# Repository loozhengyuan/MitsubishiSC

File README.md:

# MitsubishiSC

Smart controller for Mitsubishi Electric HVAC systems.

## Usage

### Upgrade

Download the app image from the [latest release](https://github.com/loozhengyuan/MitsubishiSC/releases/latest) and flash it with [`esptool`](https://docs.espressif.com/projects/esptool/), which keeps the Matter commissioning data:

```shell
esptool --chip esp32c6 write-flash 0x20000 MitsubishiSC-vX.Y.Z-fw-esp32c6-thread-app.bin
```

_NOTE: If the device does not boot after upgrading, flash the full image at `0x0` instead, which erases the Matter commissioning data. Neither image contains the per-device [factory data partition](#factory-data-partition)._

## Development

The firmware is built with [Espressif ESP-IDF](https://github.com/espressif/esp-idf) and [Espressif Matter SDK](https://github.com/espressif/esp-matter), and requires **ESP-IDF v5.5.5** to build and flash.

### Configuration

- `sdkconfig.defaults`: Baseline configuration for Matter
- `sdkconfig.debug`: Enables debug logging
- `sdkconfig.mfgpart`: Enables [Factory Data Providers](https://docs.espressif.com/projects/esp-matter/en/latest/esp32/developing.html#factory-data-providers)
- `sdkconfig.lowpower`: Enables power-saving configurations
- `sdkconfig.thread`: Enables Thread mode

```shell
idf.py -D SDKCONFIG_DEFAULTS='sdkconfig.defaults;sdkconfig.mfgpart;sdkconfig.thread' set-target 'esp32c6'
```

### Factory Data Partition

For the initial flashing, we need to generate the factory data partition using the [`esp-matter-mfg-tool`](https://github.com/espressif/esp-matter-tools/tree/main/mfg_tool). For convenience, we can use the [`./scripts/generate.sh`](./scripts/generate.sh) script:

```shell
./scripts/generate.sh
```

Thereafter, we can flash the initial factory partition (substitute `ID` based on the generated files):

```shell
idf.py flash --extra-args="0x3E0000 $(pwd)/out/fff2_8001/${ID}/${ID}-partition.bin"
```

### Build

```shell
idf.py build
```

### Flash

```shell
idf.py flash
```

### Release

The firmware and hardware share a single [semantic version](https://semver.org) in [`VERSION`](./VERSION), where `MAJOR.MINOR` is the board version. To release, bump `VERSION` in a pull request, then run the [`ci`](https://github.com/loozhengyuan/MitsubishiSC/actions/workflows/ci.yml) workflow on `main` with `release` checked.

## Concepts

### Protocol

The CN105 connector exposes the UART interface via the RX and TX pins. As [discovered by Hadley Rich](https://nicegear.nz/blog/hacking-a-mitsubishi-heat-pump-air-conditioner/), this uses 5V TTL 2400 8-E-1.

Since the ESP32/STM32 runs on 3.3V while the UART runs on 5V, there is a need to use a logic level shifter. [BSS138](https://www.onsemi.com/pdf/datasheet/bss138-d.pdf) is a N-channel MOSFET with a low $V_{GS(th)}$, which makes it [more ideal than other NMOS components](https://electronics.stackexchange.com/questions/242424/what-can-i-replace-a-bss138-n-channel-mosfet-with).

For more information about the packets, refer to [mUART Protocol Reference](https://muart-group.github.io/developer/packet-reference).

## Hardware

### MCU

As part of the project goals, we want to build a device that leverages on the [Matter](https://csa-iot.org/all-solutions/matter/) standard for maximum compatibility and [Thread](https://www.threadgroup.org) for low-power, low-latency performance. The selected microcontroller should have the following features:

- Support for WiFi and Thread
- Support for Matter over WiFi/Thread

| Manufacturer         | MPN                                                                                                                       | Type | Price                                                                                                                             |
| -------------------- | ------------------------------------------------------------------------------------------------------------------------- | ---- | --------------------------------------------------------------------------------------------------------------------------------- |
| Espressif Systems    | [`ESP32-C6FH4`](https://www.espressif.com/sites/default/files/documentation/esp32-c6_datasheet_en.pdf)                    | SoC  |                                                                                                                                   |
| Espressif Systems    | [`ESP32-C6-MINI-1`](https://www.espressif.com/sites/default/files/documentation/esp32-c6-mini-1_mini-1u_datasheet_en.pdf) | SoC  |                                                                                                                                   |
| STMicroelectronics   | [`STM32WB55CGU6`](https://www.st.com/resource/en/datasheet/stm32wb55cg.pdf)                                               | SoC  | [US$3.48](https://www.lcsc.com/product-detail/Microcontroller-Units-MCUs-MPUs-SOCs_STMicroelectronics-STM32WB55CGU6_C404023.html) |
| STMicroelectronics   | [`STM32WB5MMG`](https://www.st.com/resource/en/datasheet/stm32wb5mmg.pdf)                                                 | SoC  |                                                                                                                                   |
| Nordic Semiconductor | [`NRF52840-QIAA-R`](https://docs-be.nordicsemi.com/bundle/ps_nrf52840/attach/nRF52840_PS_v1.9.pdf)                        | SoC  | [US$3.41](https://www.lcsc.com/product-detail/RF-Transceiver-ICs_Nordic-Semicon-NRF52840-QIAA-R_C190794.html)                     |

_NOTE: The SKUs from [LCSC](https://www.lcsc.com) Popular Products are preferred to ensure good price and supply._

### Connector

The Mitsubishi Electric air conditioner has a `CN105` port that appears to be a [JST PA](https://www.jst.com/products/appliance-connectors/pa-family/) connector. To fit this, we should use `PAP-05V-S` housing with `SPHD-001T-P0.5`/`SPHD-002T-P0.5` contacts.

DigiKey stocks the `APALPA22K305`/`APAPA22K305` pre-crimped cables in 22 AWG, 12" cables.

According to the [LCSC](https://www.lcsc.com) team, the HCTL [`HC-PA-5Y`](https://www.lcsc.com/product-detail/Rectangular-Connectors-Housings_HCTL_C2962360.html) and [`HC-PA-T`](https://www.lcsc.com/product-detail/Line-Pressing-Terminals_HCTL-HC-PA-T_C2962368.html) are equivalent replacements for this part.

### Power Supply

The STM32/ESP32 runs on 3.3V but the `CN105` connector only exposes 12V and 5V power rails.

To power the MCU, we use a low-dropout linear regulator to regulate 5V to 3.3V. `MCP1700` is chosen for its low quiescent current ($I_Q$) but any modern LDO should work.

## License

[MIT](https://choosealicense.com/licenses/mit/)

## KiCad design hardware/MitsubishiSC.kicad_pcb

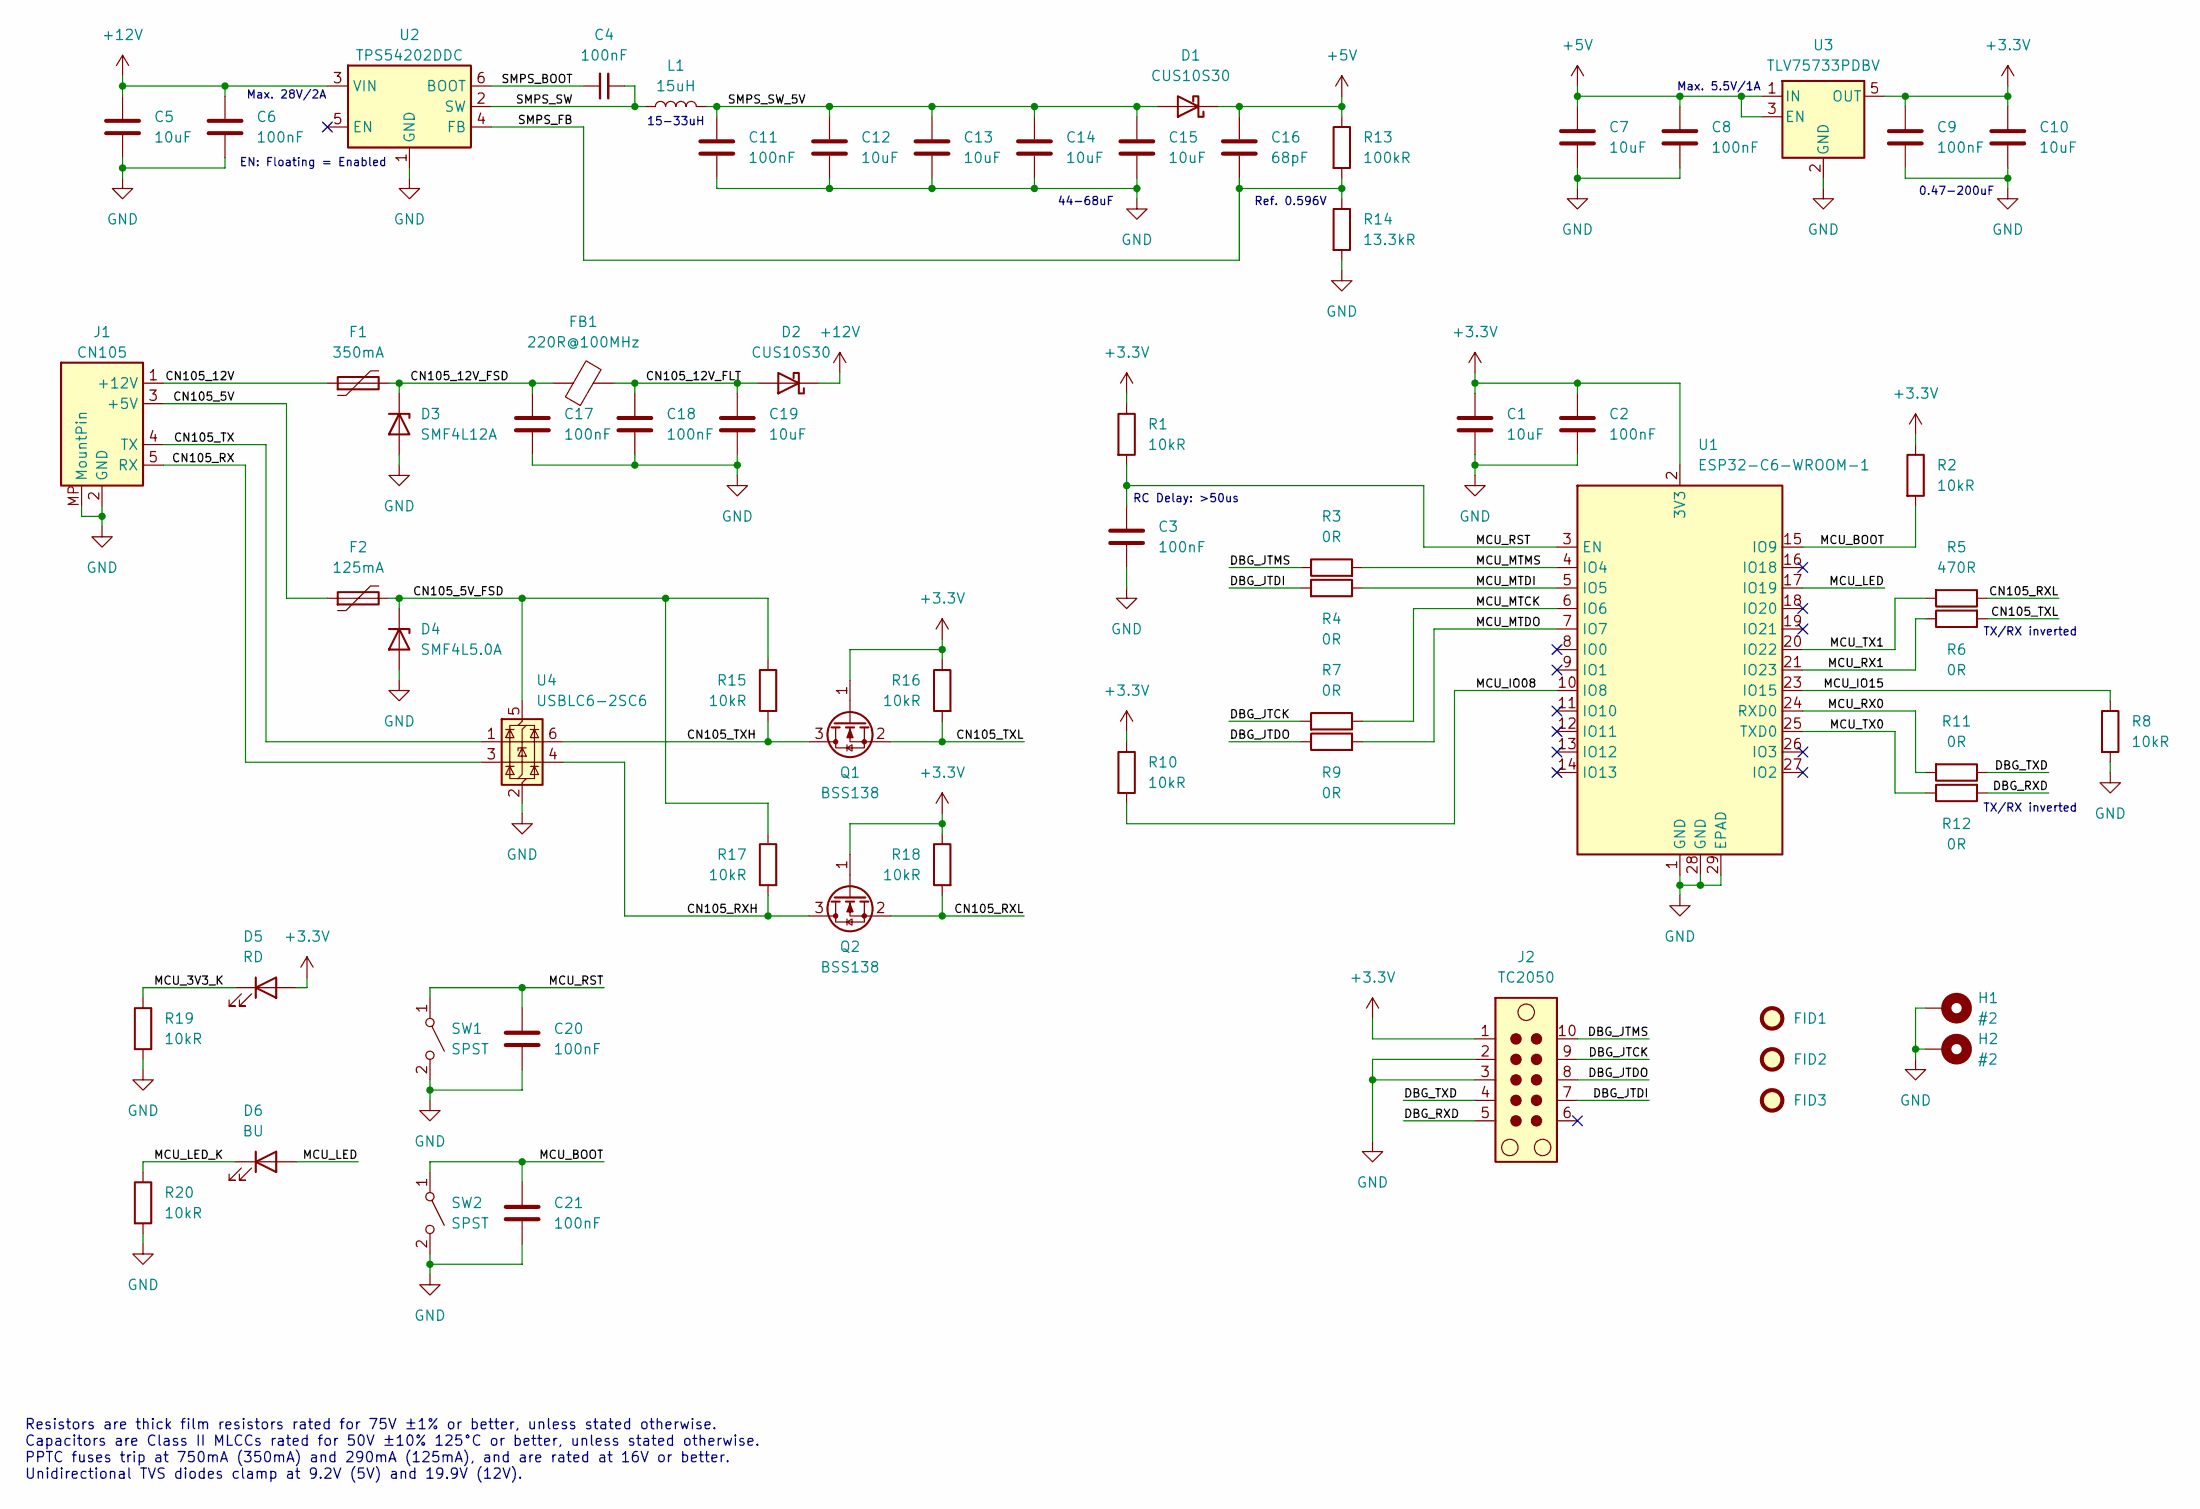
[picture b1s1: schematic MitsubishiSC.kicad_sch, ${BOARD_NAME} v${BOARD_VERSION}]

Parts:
C1, C5, C7, C10, C12, C13, C14, C15, C19: 10uF; C_1206_3216Metric; Manufacturer Part Number CL31B106KBHNNNE
C2, C3, C4, C6, C8, C9, C11, C17, C18, C20, C21: 100nF; C_0603_1608Metric; Manufacturer Part Number CL10B104KC8NNNC
C16: 68pF; C_0603_1608Metric; Manufacturer Part Number CL10C680JB8NNNC
D1, D2: CUS10S30; D_SOD-323; Manufacturer Part Number CUS10S30,H3F
D3: SMF4L12A; D_SOD-123F; Manufacturer Part Number SMF4L12A
D4: SMF4L5.0A; D_SOD-123F; Manufacturer Part Number SMF4L5.0A
D5: RD; LED_0805_2012Metric; Manufacturer Part Number XL-2012SURC
D6: BU; LED_0805_2012Metric; Manufacturer Part Number XL-2012UBC
F1: 350mA; Fuse_1206_3216Metric; Manufacturer Part Number 1206L035/16YR
F2: 125mA; Fuse_1206_3216Metric; Manufacturer Part Number 1206L012WR
FB1: 220R@100MHz; L_0805_2012Metric; Manufacturer Part Number BLM21PG221SN1D
FID1, FID2, FID3: Fiducial; Fiducial_1mm_Mask2mm
H1, H2: #2; MountingHole_2.5mm_Pad_Via; Manufacturer Part Number 1553WTS100
J1: CN105; JST_PA_SM05B-PASS_1x05-1MP_P2.00mm_Horizontal; Manufacturer Part Number SM05B-PASS-TBT(LF)(SN)
J2: TC2050; Tag-Connect_TC2050-IDC-NL_2x05_P1.27mm_Vertical
L1: 15uH; L_TDK_VLS6045EX_VLS6045AF; Manufacturer Part Number VLS6045EX-150M
Q1, Q2: BSS138; SOT-23; Manufacturer Part Number BSS138
R1, R2, R8, R10, R15, R16, R17, R18, R19, R20: 10kR; R_0603_1608Metric; Manufacturer Part Number RC0603FR-0710KL
R3, R4, R6, R7, R9, R11, R12: 0R; R_0603_1608Metric; Manufacturer Part Number RC0603FR-070RL
R5: 470R; R_0603_1608Metric; Manufacturer Part Number RC0603FR-07470RL
R13: 100kR; R_0603_1608Metric; Manufacturer Part Number RC0603FR-07100KL
R14: 13.3kR; R_0603_1608Metric; Manufacturer Part Number RC0603FR-0713K3L
SW1, SW2: SPST; SW_SPST_PTS810; Manufacturer Part Number GT-TC048D-H025-L1
U1: ESP32-C6-WROOM-1; Manufacturer Part Number ESP32-C6-WROOM-1-N8
U2: TPS54202DDC; SOT-23-6; Manufacturer Part Number TPS54202DDCR
U3: TLV75733PDBV; SOT-23-5; Manufacturer Part Number TLV75733PDBVR
U4: USBLC6-2SC6; SOT-23-6; Manufacturer Part Number USBLC6-2SC6

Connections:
+3.3V: C1.1, C2.1, C9.1, C10.1, D5.2 (A), J2.1, Q1.1 (G), Q2.1 (G), R1.1, R2.1, R10.1, R16.1, R18.1, U1.2 (3V3), U3.5 (OUT)
+5V: C7.1, C8.1, C16.1, D1.1 (K), R13.1, U3.1 (IN), U3.3 (EN)
+12V: C5.1, C6.1, D2.1 (K), U2.3 (VIN)
/CN105_5V: F2.1, J1.3 (+5V)
/CN105_5V_FSD: D4.1 (K), F2.2, R15.1, R17.1, U4.5 (VBUS)
/CN105_12V: F1.1, J1.1 (+12V)
/CN105_12V_FLT: C18.1, C19.1, D2.2 (A), FB1.2
/CN105_12V_FSD: C17.1, D3.1 (K), F1.2, FB1.1
/CN105_RX: J1.5 (RX), U4.3 (I/O2)
/CN105_RXH: Q2.3 (D), R17.2, U4.4 (I/O2)
/CN105_RXL: Q2.2 (S), R5.1, R18.2
/CN105_TX: J1.4 (TX), U4.1 (I/O1)
/CN105_TXH: Q1.3 (D), R15.2, U4.6 (I/O1)
/CN105_TXL: Q1.2 (S), R6.2, R16.2
/DBG_JTCK: J2.9, R7.2
/DBG_JTDI: J2.7, R4.2
/DBG_JTDO: J2.8, R9.1
/DBG_JTMS: J2.10, R3.1
/DBG_RXD: J2.5, R12.2
/DBG_TXD: J2.4, R11.1
/MCU_3V3_K: D5.1 (K), R19.1
/MCU_BOOT: C21.1, R2.2, SW2.1 (A), U1.15 (IO9)
/MCU_IO08: R10.2, U1.10 (IO8)
/MCU_IO15: R8.1, U1.23 (IO15)
/MCU_LED: D6.2 (A), U1.17 (IO19)
/MCU_LED_K: D6.1 (K), R20.1
/MCU_MTCK: R7.1, U1.6 (IO6)
/MCU_MTDI: R4.1, U1.5 (IO5)
/MCU_MTDO: R9.2, U1.7 (IO7)
/MCU_MTMS: R3.2, U1.4 (IO4)
/MCU_RST: C3.1, C20.1, R1.2, SW1.1 (A), U1.3 (EN)
/MCU_RX0: R11.2, U1.24 (RXD0)
/MCU_RX1: R6.1, U1.21 (IO23)
/MCU_TX0: R12.1, U1.25 (TXD0)
/MCU_TX1: R5.2, U1.20 (IO22)
/SMPS_BOOT: C4.1, U2.6 (BOOT)
/SMPS_FB: C16.2, R13.2, R14.1, U2.4 (FB)
/SMPS_SW: C4.2, L1.1, U2.2 (SW)
/SMPS_SW_5V: C11.1, C12.1, C13.1, C14.1, C15.1, D1.2 (A), L1.2
GND: C1.2, C2.2, C3.2, C5.2, C6.2, C7.2, C8.2, C9.2, C10.2, C11.2, C12.2, C13.2, C14.2, C15.2, C17.2, C18.2, C19.2, C20.2, C21.2, D3.2 (A), D4.2 (A), H1.1 (1_1), H2.1 (1_1), J1.2 (GND), J1.MP (MountPin), J2.2, J2.3, R8.2, R14.2, R19.2, R20.2, SW1.2 (B), SW2.2 (B), U1.1 (GND), U1.28 (GND), U1.29 (EPAD), U2.1 (GND), U3.2 (GND), U4.2 (GND)

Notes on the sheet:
TX/RX inverted
15-33uH
Ref. 0.596V
EN: Floating = Enabled
Max. 28V/2A
Max. 5.5V/1A
0.47-200uF
44-68uF
Resistors are thick film resistors rated for 75V ±1% or better, unless stated otherwise. Capacitors are Class II MLCCs rated for 50V ±10% 125°C or better, unless stated otherwise. PPTC fuses trip at 750mA (350mA) and 290mA (125mA), and are rated at 16V or better. Unidirectional TVS diodes clamp at 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
RC Delay: >50us

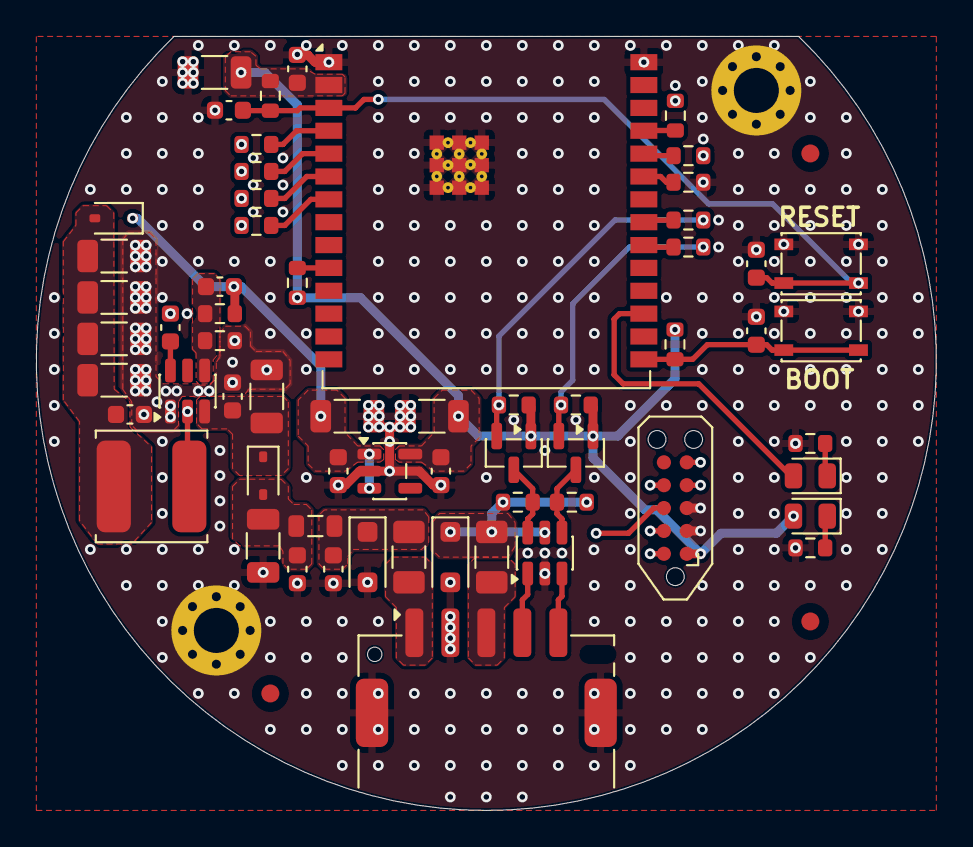
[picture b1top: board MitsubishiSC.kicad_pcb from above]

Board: 6 copper layers, 50.0 x 43.0 mm, 66 parts (0 on the bottom side), 40 nets.

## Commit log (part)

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2024-05-05 chore: initial repo setup
2024-05-19 docs: add info on packet reference
2024-09-14 chore(deps): add deps for Zephyr project
2024-09-17 feat: switch board to STM32WB55RG
2024-12-22 feat: add HomeSpan impln via Arduino CLI
2025-02-09 chore: add tooling files
2025-03-29 chore(deps): bump actions/setup-python in the minor group (#3)
    Bumps the minor group with 1 update: [actions/setup-python](https://github.com/actions/setup-python).
    Updates `actions/setup-python` from 5.4.0 to 5.5.0
    - [Release notes](https://github.com/actions/setup-python/releases)
    - [Commits](https://github.com/actions/setup-python/compare/v5.4.0...v5.5.0)
    ---
    updated-dependencies:
2025-05-10 chore(deps): bump dependabot/fetch-metadata in the minor group
    Bumps the minor group with 1 update: [dependabot/fetch-metadata](https://github.com/dependabot/fetch-metadata).
    Updates `dependabot/fetch-metadata` from 2.3.0 to 2.4.0
    - [Release notes](https://github.com/dependabot/fetch-metadata/releases)
    - [Commits](https://github.com/dependabot/fetch-metadata/compare/v2.3.0...v2.4.0)
    ---
    updated-dependencies:
2025-08-16 chore(deps): bump actions/checkout from 4.2.2 to 5.0.0 (#6)
    Bumps [actions/checkout](https://github.com/actions/checkout) from 4.2.2 to 5.0.0.
    - [Release notes](https://github.com/actions/checkout/releases)
    - [Changelog](https://github.com/actions/checkout/blob/main/CHANGELOG.md)
    - [Commits](https://github.com/actions/checkout/compare/v4.2.2...v5.0.0)
    ---
    updated-dependencies:
2025-08-25 chore: update github config (#8)
    This commit removes `has_issues` because it was recently re-enabled.
    Trace-Id: 3a8621aa3f26bfdbd8048a3661baacfb
2025-09-06 chore(deps): bump actions/setup-python from 5.6.0 to 6.0.0
    Bumps [actions/setup-python](https://github.com/actions/setup-python) from 5.6.0 to 6.0.0.
    - [Release notes](https://github.com/actions/setup-python/releases)
    - [Commits](https://github.com/actions/setup-python/compare/v5.6.0...v6.0.0)
    ---
    updated-dependencies:
    - dependency-name: actions/setup-python
2025-09-17 chore(deps): bump actions/upload-artifact in the minor group
    Bumps the minor group with 1 update: [actions/upload-artifact](https://github.com/actions/upload-artifact).
    Updates `actions/upload-artifact` from 4.6.0 to 4.6.2
    - [Release notes](https://github.com/actions/upload-artifact/releases)
    - [Commits](https://github.com/actions/upload-artifact/compare/v4.6.0...v4.6.2)
    ---
    updated-dependencies:
2025-09-17 feat: upgrade to KiCad v9 (#14)
    This commit upgrades the KiCad files to `9.0.4`.
2025-09-18 feat(hw): enable 3D model/render exports
    This commit adds support for exporting 3D renders and models for PCB.
2025-09-18 fix(hw): swap C6/C17 cap placement (#17)
    This commit fixes an issue with the SMPS output cap placement where the
    100nF capacitor should have been placed closest to the pins but is not
    the case.
2025-09-19 fix(hw): incorrect PPTC footprint (#19)
    This commit fixes the incorrect PPTC footprint size.
    The existing schematic specifies the Bourns MF-MSMF030-2 part which
    should be using the `Fuse_1812_4532Metric` footprint but was instead
    assigned the `Fuse_1206_3216Metric` footprint. As a result, the
    component CANNOT be placed on the circuit board.
    To rectify this, we changed the component to use the Littelfuse
2025-09-20 chore(deps): bump hardware/lib from `199c1e1` to `e7fd264`
    Bumps [hardware/lib](https://github.com/loozhengyuan/kicad) from `199c1e1` to `e7fd264`.
    - [Commits](https://github.com/loozhengyuan/kicad/compare/199c1e1a25dc3f4a231f425dc5fd3ef8ca8db975...e7fd264120bbb1a4f89bc8e4ca3f54ad22f7fd1c)
    ---
    updated-dependencies:
    - dependency-name: hardware/lib
    dependency-version: e7fd264120bbb1a4f89bc8e4ca3f54ad22f7fd1c
2025-09-20 ci: bump to ubuntu-24.04
    This commit updates the repositories to use `ubuntu-24.04` runner type.
    Idempotency-Key: b65e24792f1426145cd7e87ec4b34af8f1f8997b122f0173c1f5dc88a97e9c97
2025-09-27 chore(deps): bump hardware/lib from `e7fd264` to `23258cb`
    Bumps [hardware/lib](https://github.com/loozhengyuan/kicad) from `e7fd264` to `23258cb`.
    - [Commits](https://github.com/loozhengyuan/kicad/compare/e7fd264120bbb1a4f89bc8e4ca3f54ad22f7fd1c...23258cb61563da85fa9d046a8a65338788b5317a)
    ---
    updated-dependencies:
    - dependency-name: hardware/lib
    dependency-version: 23258cb61563da85fa9d046a8a65338788b5317a
2025-10-13 chore: update GitHub repo config (#25)
    This commit standardises the GitHub repo config across
    repositories. Apart from inconsequential changes, it
    includes several noteworthy modifications:
    - Add `require-signed-commits` ruleset to cater for LLMs
    - Modify `collaborators` ruleset to `require-status-checks`
    - Enforce squash commit format
2025-10-25 chore(deps): bump actions/upload-artifact from 4.6.2 to 5.0.0
    Bumps [actions/upload-artifact](https://github.com/actions/upload-artifact) from 4.6.2 to 5.0.0.
    - [Release notes](https://github.com/actions/upload-artifact/releases)
    - [Commits](https://github.com/actions/upload-artifact/compare/ea165f8d65b6e75b540449e92b4886f43607fa02...330a01c490aca151604b8cf639adc76d48f6c5d4)
    ---
    updated-dependencies:
    - dependency-name: actions/upload-artifact
2025-11-22 chore(deps): bump hardware/lib from `4d18a40` to `52a9a50`
    Bumps [hardware/lib](https://github.com/loozhengyuan/kicad) from `4d18a40` to `52a9a50`.
    - [Commits](https://github.com/loozhengyuan/kicad/compare/4d18a40f2ec891081f94f9c6d18aeea6f3f264a1...52a9a50c2a1da3880ab78c090232d2913ed1f7e4)
    ---
    updated-dependencies:
    - dependency-name: hardware/lib
    dependency-version: 52a9a50c2a1da3880ab78c090232d2913ed1f7e4
2025-11-29 chore(deps): bump actions/setup-python in the minor group (#30)
    Bumps the minor group with 1 update: [actions/setup-python](https://github.com/actions/setup-python).
    Updates `actions/setup-python` from 6.0.0 to 6.1.0
    - [Release notes](https://github.com/actions/setup-python/releases)
    - [Commits](https://github.com/actions/setup-python/compare/e797f83bcb11b83ae66e0230d6156d7c80228e7c...83679a892e2d95755f2dac6acb0bfd1e9ac5d548)
    ---
    updated-dependencies:
2025-12-06 chore(deps): bump actions/checkout in the minor group (#31)
    Bumps the minor group with 1 update: [actions/checkout](https://github.com/actions/checkout).
    Updates `actions/checkout` from 6.0.0 to 6.0.1
    - [Release notes](https://github.com/actions/checkout/releases)
    - [Changelog](https://github.com/actions/checkout/blob/main/CHANGELOG.md)
    - [Commits](https://github.com/actions/checkout/compare/1af3b93b6815bc44a9784bd300feb67ff0d1eeb3...8e8c483db84b4bee98b60c0593521ed34d9990e8)
    ---
2025-12-22 chore(deps): bump hardware/lib from `768aa73` to `c08543f`
    Bumps [hardware/lib](https://github.com/loozhengyuan/kicad) from `768aa73` to `c08543f`.
    - [Commits](https://github.com/loozhengyuan/kicad/compare/768aa733a1ab6b95ad2dd7de75842aa46bf29dfb...c08543ffaef004d701582646cdbe2edbb014a9bf)
    ---
    updated-dependencies:
    - dependency-name: hardware/lib
    dependency-version: c08543ffaef004d701582646cdbe2edbb014a9bf
2026-01-03 chore(deps): bump hardware/lib from `c08543f` to `dacaa1f` (#36)
    Bumps [hardware/lib](https://github.com/loozhengyuan/kicad) from `c08543f` to `dacaa1f`.
    - [Commits](https://github.com/loozhengyuan/kicad/compare/c08543ffaef004d701582646cdbe2edbb014a9bf...dacaa1fac1e62226a4627610998bff69c53f02f0)
    ---
    updated-dependencies:
    - dependency-name: hardware/lib
    dependency-version: dacaa1fac1e62226a4627610998bff69c53f02f0
2026-01-10 feat(pcb): revamp design and layout
    This commit makes significant changes to the PCB, primarily changing the
    MCU from ESP32-C3 to ESP32-C6 to accommodate Matter-over-Thread.
2026-01-17 chore(deps): bump hardware/lib from `dacaa1f` to `3c105d8`
    Bumps [hardware/lib](https://github.com/loozhengyuan/kicad) from `dacaa1f` to `3c105d8`.
    - [Commits](https://github.com/loozhengyuan/kicad/compare/dacaa1fac1e62226a4627610998bff69c53f02f0...3c105d891bb64ac8d859a714ecf152926401822e)
    ---
    updated-dependencies:
    - dependency-name: hardware/lib
    dependency-version: 3c105d891bb64ac8d859a714ecf152926401822e
2026-01-24 chore(deps): bump the minor group with 2 updates (#40)
    Bumps the minor group with 2 updates: [actions/checkout](https://github.com/actions/checkout) and [actions/setup-python](https://github.com/actions/setup-python).
    Updates `actions/checkout` from 6.0.1 to 6.0.2
    - [Release notes](https://github.com/actions/checkout/releases)
    - [Changelog](https://github.com/actions/checkout/blob/main/CHANGELOG.md)
    - [Commits](https://github.com/actions/checkout/compare/8e8c483db84b4bee98b60c0593521ed34d9990e8...de0fac2e4500dabe0009e67214ff5f5447ce83dd)
    Updates `actions/setup-python` from 6.1.0 to 6.2.0
2026-02-17 feat: redesign PCB layout
2026-02-28 chore(deps): bump actions/upload-artifact from 6.0.0 to 7.0.0
    Bumps [actions/upload-artifact](https://github.com/actions/upload-artifact) from 6.0.0 to 7.0.0.
    - [Release notes](https://github.com/actions/upload-artifact/releases)
    - [Commits](https://github.com/actions/upload-artifact/compare/b7c566a772e6b6bfb58ed0dc250532a479d7789f...bbbca2ddaa5d8feaa63e36b76fdaad77386f024f)
    ---
    updated-dependencies:
    - dependency-name: actions/upload-artifact
2026-03-28 chore(deps): bump dependabot/fetch-metadata from 2.5.0 to 3.0.0 (#45)
    Bumps [dependabot/fetch-metadata](https://github.com/dependabot/fetch-metadata) from 2.5.0 to 3.0.0.
    - [Release notes](https://github.com/dependabot/fetch-metadata/releases)
    - [Commits](https://github.com/dependabot/fetch-metadata/compare/21025c705c08248db411dc16f3619e6b5f9ea21a...ffa630c65fa7e0ecfa0625b5ceda64399aea1b36)
    ---
    updated-dependencies:
    - dependency-name: dependabot/fetch-metadata
2026-04-11 chore(deps): bump actions/upload-artifact in the minor group
    Bumps the minor group with 1 update: [actions/upload-artifact](https://github.com/actions/upload-artifact).
    Updates `actions/upload-artifact` from 7.0.0 to 7.0.1
    - [Release notes](https://github.com/actions/upload-artifact/releases)
    - [Commits](https://github.com/actions/upload-artifact/compare/bbbca2ddaa5d8feaa63e36b76fdaad77386f024f...043fb46d1a93c77aae656e7c1c64a875d1fc6a0a)
    ---
    updated-dependencies:
2026-05-02 chore(deps): bump hardware/lib from `a191e8d` to `82a9912`
    Bumps [hardware/lib](https://github.com/loozhengyuan/kicad) from `a191e8d` to `82a9912`.
    - [Commits](https://github.com/loozhengyuan/kicad/compare/a191e8d5fcce252213ee0e27be27f5f9fa198df7...82a9912089d8d552c4fbbd3c74eb551834488c75)
    ---
    updated-dependencies:
    - dependency-name: hardware/lib
    dependency-version: 82a9912089d8d552c4fbbd3c74eb551834488c75
2026-06-06 chore(deps): bump actions/checkout in the minor group (#50)
    Bumps the minor group with 1 update: [actions/checkout](https://github.com/actions/checkout).
    Updates `actions/checkout` from 6.0.2 to 6.0.3
    - [Release notes](https://github.com/actions/checkout/releases)
    - [Changelog](https://github.com/actions/checkout/blob/main/CHANGELOG.md)
    - [Commits](https://github.com/actions/checkout/compare/de0fac2e4500dabe0009e67214ff5f5447ce83dd...df4cb1c069e1874edd31b4311f1884172cec0e10)
    ---
2026-06-20 chore(deps): bump actions/checkout from 6.0.3 to 7.0.0
    Bumps [actions/checkout](https://github.com/actions/checkout) from 6.0.3 to 7.0.0.
    - [Release notes](https://github.com/actions/checkout/releases)
    - [Changelog](https://github.com/actions/checkout/blob/main/CHANGELOG.md)
    - [Commits](https://github.com/actions/checkout/compare/df4cb1c069e1874edd31b4311f1884172cec0e10...9c091bb21b7c1c1d1991bb908d89e4e9dddfe3e0)
    ---
    updated-dependencies:
